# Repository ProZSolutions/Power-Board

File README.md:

# Power-Board
ams1117 LDO 3.3v and 5v with 750 milli amp fuse

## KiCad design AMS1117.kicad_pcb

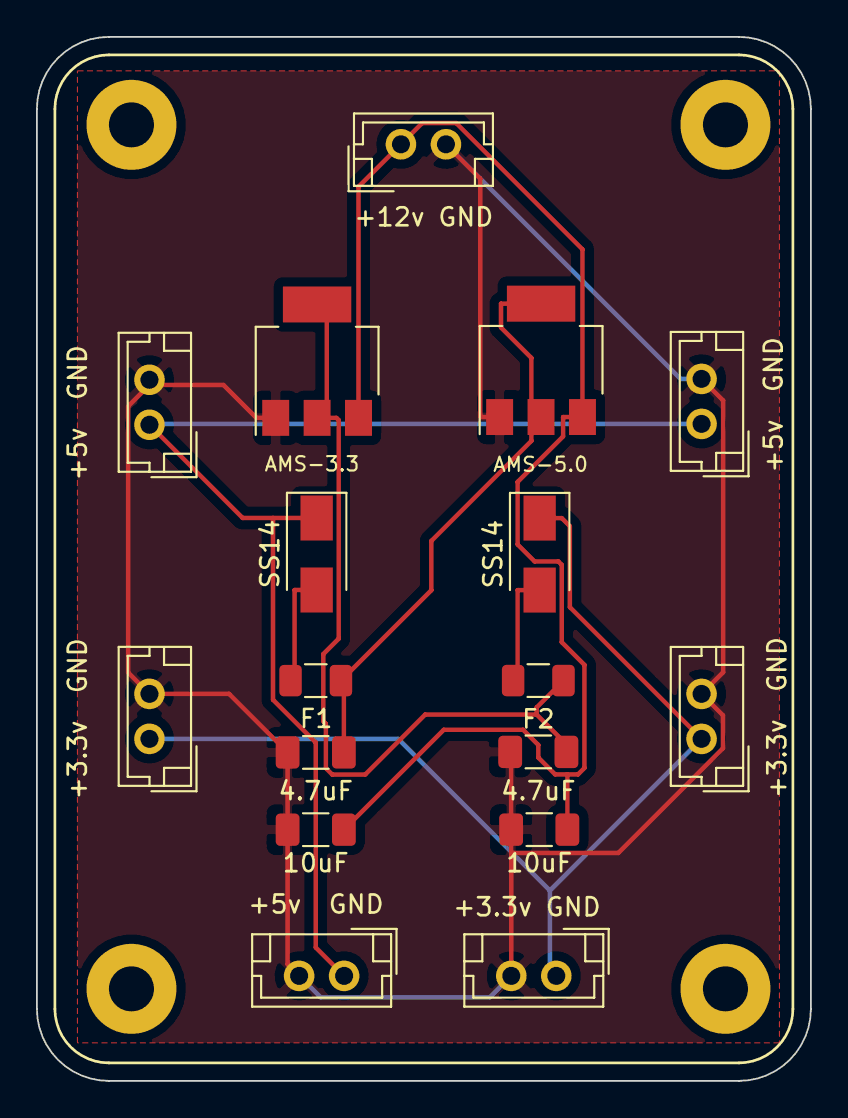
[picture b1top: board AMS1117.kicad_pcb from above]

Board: 2 copper layers, 43.0 x 58.0 mm, 21 parts (0 on the bottom side), 8 nets.

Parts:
+3.3v  GND, +5v  GND: Conn_01x02; JST_EH_B2B-EH-A_1x02_P2.50mm_Vertical
C1, C2: 10uF; C_1206_3216Metric_Pad1.33x1.80mm_HandSolder
C3, C4: 4.7uF; C_1206_3216Metric_Pad1.33x1.80mm_HandSolder
D1, D2: SS14; D_SMA
F1, F2: 750mA; Fuse_1206_3216Metric
H1, H2, H3, H4: MountingHole; MountingHole_2.5mm_Pad
J1, J2, J3, J4, J5: Conn_01x02; JST_EH_B2B-EH-A_1x02_P2.50mm_Vertical
U1: AMS1117-5.0; SOT-223-3_TabPin2
U2: AMS1117-3.3; SOT-223-3_TabPin2

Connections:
+3V3: +3.3v GND.1, D2.1, J2.1, J4.1
+5V: +5v GND.1, D1.1, J3.1, J5.1
+12V: C1.1, C2.1, J1.1, U1.3, U2.3
GND: +3.3v GND.2, +5v GND.2, C1.2, C2.2, C3.2, C4.2, J1.2, J2.2, J3.2, J4.2, J5.2, U1.1, U2.1
unnamed: C3.1, F1.2, U1.2
unnamed: C4.1, F2.2, U2.2
unnamed: D1.2, F1.1
unnamed: D2.2, F2.1

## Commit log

2021-07-12 Board Picture
